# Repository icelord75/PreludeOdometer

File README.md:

# PreludeOdometer

Dot matrix LED display replacement for mechanical odometer in Honda Prelude IV

## Supported modes:
 - Arduino Nano328 controller
 - Precise configure wheel/VSS ratio
 - Total mileage
 - A/B trip (up to 9999.9km)
 - Motor hours counter
 - Configurable LED needle illumination with dimming feature
 - Configurable Electroluminescence instrumental cluster illumination controller
 - Outside Temperature (DS1820 sensor)

## License

**PreludeOdometer** is available under GPL License.

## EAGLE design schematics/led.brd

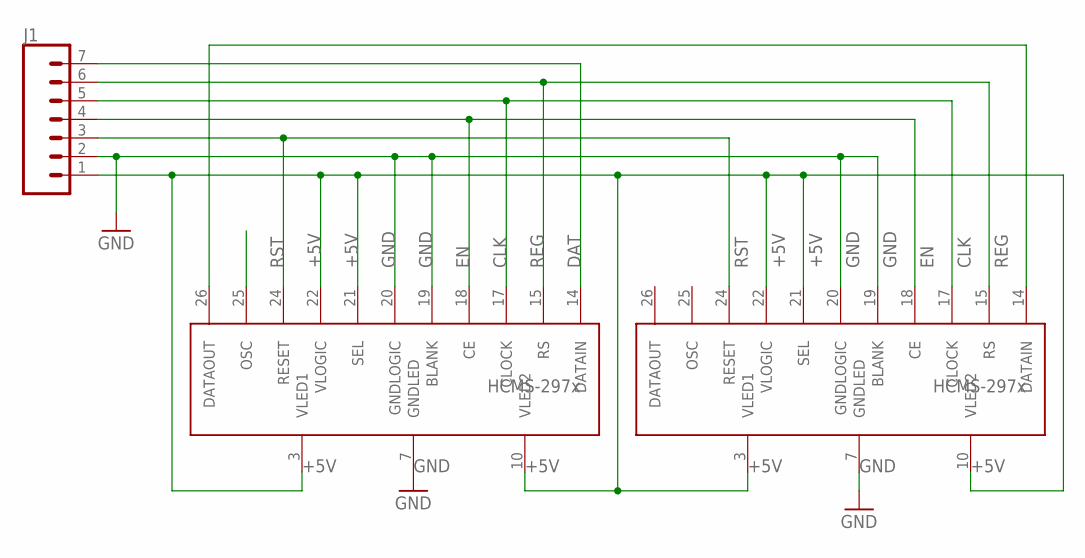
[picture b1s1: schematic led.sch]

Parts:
J1: CONN_07LONGPADS; 1X07_LONGPADS
U$1, U$2: HCMS-297X

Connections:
+5V: J1.1, U$1.3 (VLED1), U$1.10 (VLED2), U$1.21 (SEL), U$1.22 (VLOGIC), U$2.3 (VLED1), U$2.10 (VLED2), U$2.21 (SEL), U$2.22 (VLOGIC)
CLK: J1.5, U$1.17 (CLOCK), U$2.17 (CLOCK)
DAT: J1.7, U$1.14 (DATAIN)
EN: J1.4, U$1.18 (CE), U$2.18 (CE)
GND: J1.2, U$1.7 (GNDLED), U$1.19 (BLANK), U$1.20 (GNDLOGIC), U$2.7 (GNDLED), U$2.19 (BLANK), U$2.20 (GNDLOGIC)
unnamed: U$1.26 (DATAOUT), U$2.14 (DATAIN)
REG: J1.6, U$1.15 (RS), U$2.15 (RS)
RST: J1.3, U$1.24 (RESET), U$2.24 (RESET)

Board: 2 copper layers, 3 parts (0 on the bottom side), 8 nets, no tracks yet.

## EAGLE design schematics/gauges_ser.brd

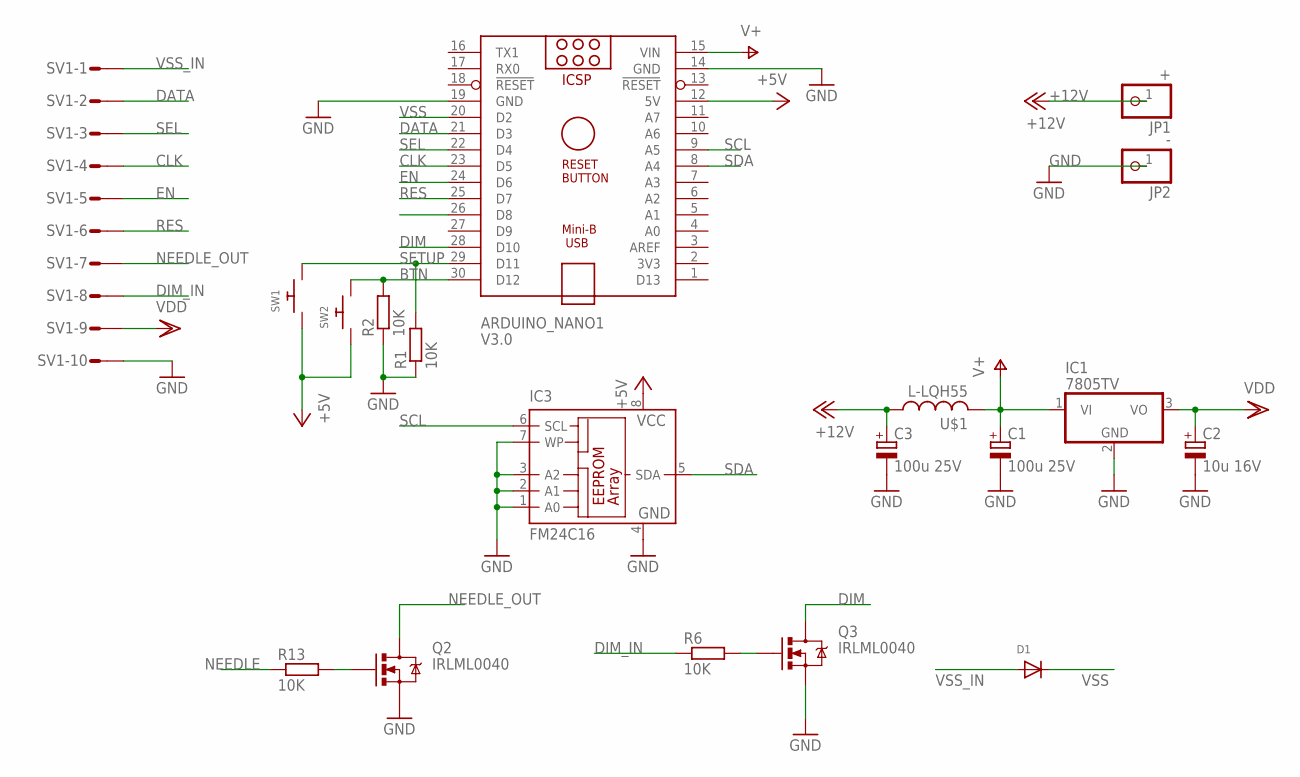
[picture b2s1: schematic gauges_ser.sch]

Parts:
ARDUINO_NANO1: V3.0; ARDUINO_NANO
C1, C3: 100u 25V; SMC_D
C2: 10u 16V; SMC_B
D1: DIODESOD-123; SOD-123
IC1: 7805TV; TO220V
IC3: FM24C16; SO-08M
JP1: +; 1X01
JP2: -; 1X01
Q2, Q3: IRLML0040; SOT23-3
R1, R2, R6, R13: 10K; R0805
SV1: L10P
SW1, SW2: SWITCH_PUSHBUTTONEVQ-PE; TACT_PANA-EVQ
U$1: L-LQH55; LQH55

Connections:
+5V: ARDUINO_NANO1.12 (5V), IC3.8 (VCC), SW1.P$1, SW2.P$1
+12V: C3.+, JP1.1, U$1.1
BTN: ARDUINO_NANO1.30 (D12), R2.2, SW2.P$2
CLK: ARDUINO_NANO1.23 (D5), SV1.4
DATA: ARDUINO_NANO1.21 (D3), SV1.2
DIM: ARDUINO_NANO1.28 (D10), Q3.3 (D)
DIM_IN: R6.1, SV1.8
EN: ARDUINO_NANO1.24 (D6), SV1.5
GND: ARDUINO_NANO1.14 (GND), ARDUINO_NANO1.19 (GND), C1.-, C2.-, C3.-, IC1.2 (GND), IC3.1 (A0), IC3.2 (A1), IC3.3 (A2), IC3.4 (GND), IC3.7 (WP), JP2.1, Q2.2 (S), Q3.2 (S), R1.1, R2.1, SV1.10
unnamed: Q2.1 (G), R13.2
unnamed: Q3.1 (G), R6.2
NEEDLE: ARDUINO_NANO1.26 (D8), R13.1
NEEDLE_OUT: Q2.3 (D), SV1.7
RES: ARDUINO_NANO1.25 (D7), SV1.6
SCL: ARDUINO_NANO1.9 (A5), IC3.6 (SCL)
SDA: ARDUINO_NANO1.8 (A4), IC3.5 (SDA)
SEL: ARDUINO_NANO1.22 (D4), SV1.3
SETUP: ARDUINO_NANO1.29 (D11), R1.2, SW1.P$2
V+: ARDUINO_NANO1.15 (VIN), C1.+, IC1.1 (VI), U$1.2
VDD: C2.+, IC1.3 (VO), SV1.9
VSS: ARDUINO_NANO1.20 (D2), D1.C
VSS_IN: D1.A, SV1.1

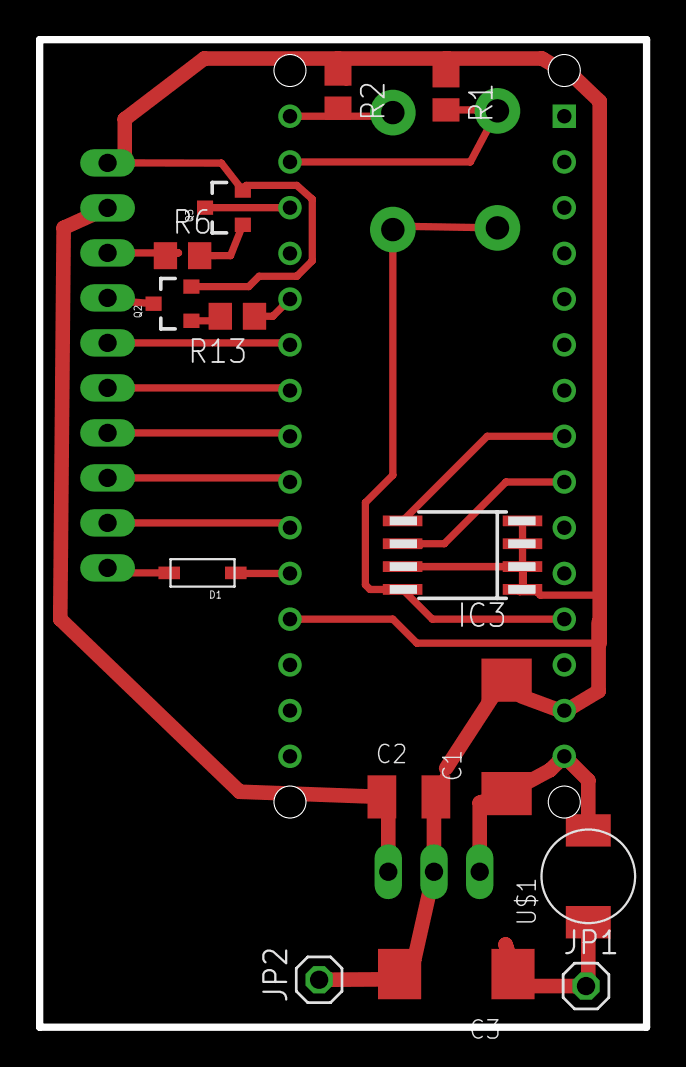
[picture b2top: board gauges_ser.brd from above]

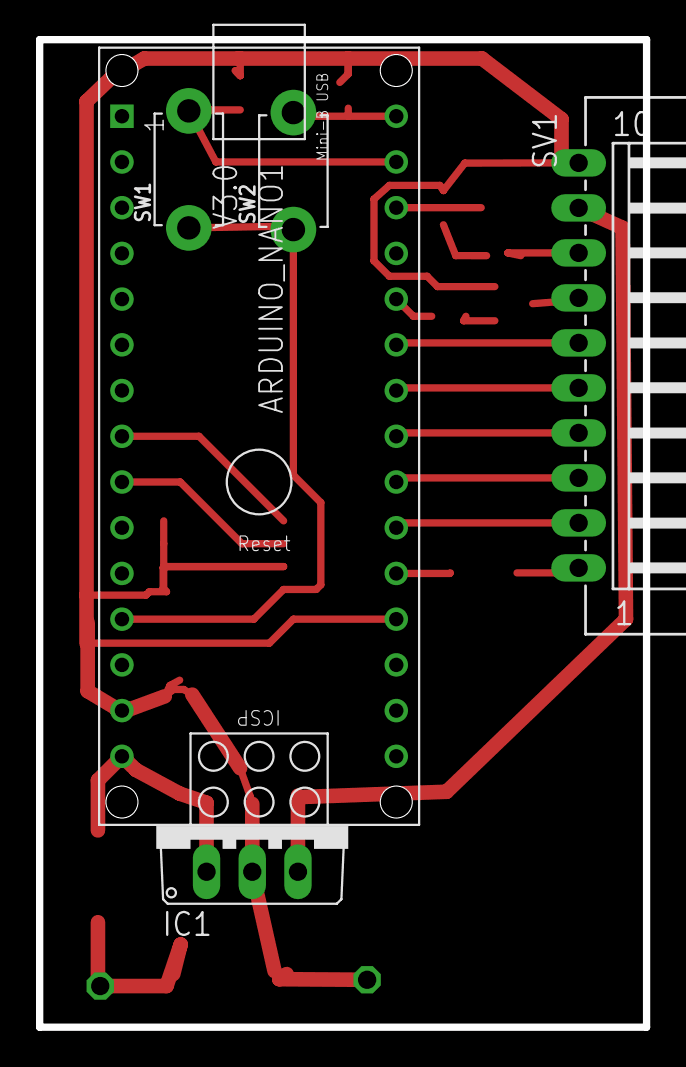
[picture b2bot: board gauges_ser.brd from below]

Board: 2 copper layers, 33.7 x 54.9 mm, 19 parts (5 on the bottom side), 22 nets.

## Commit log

2017-08-01 Initial
2017-08-08 syntax errors
2017-08-16 minor fixes
2017-08-24 updates motor hours counter
2017-08-24 readme update
2017-08-24 beatyfication
2017-08-26 Cross board schematics
2017-08-27 fixes
2017-08-27 updates fix multi devices brightness
2017-08-27 fixes and updates
2017-08-27 LED Display text fitting
2017-08-28 Dimming alarm and fixes
2017-09-07 rpm counter fix
2017-09-12 add tem sensor and minor fixes
2017-09-20 LedDisplay moved internaly + font mods
2017-09-20 minor updates
2017-09-20 outside temp added and indiglo controll
2017-09-20 boards wiring added
2017-09-21 schematics addon
2017-09-21 bug fixes
2017-09-21 bug fix and WDT for optiboot
2017-10-22 process
2018-07-22 correct vss pulsing
2019-04-22 some
2024-08-18 new file name

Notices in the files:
parts and their libraries:
SparkFun-DiscreteSemi: Licensing: Creative Commons ShareAlike 4.0 International - https://creativecommons.org/licenses/by-sa/4.0
